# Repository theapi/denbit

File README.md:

# Denbit
Training wheels for the NodeMCU
-------------------------------------------------------------

##Installation

- Download and install the [Aduino IDE](https://www.arduino.cc/en/Main/Software) plus any drivers it asks too. 
 You can use the free version with the `JUST DOWNLOAD` link. No need to donate money.

- Install the NodeMCU "board" into the Arduino IDE:
 - Start Arduino and open Preferences window.
 - Enter http://arduino.esp8266.com/stable/package_esp8266com_index.json into Additional Board Manager URLs field and click `Ok`:

 - Open the Boards Manager `Tools > Board > Boards Manager...`:

 - Scroll down to `esp8266 by ESP8266 Community`, click `More info` and select version 2.2.0 then click install:

 - Click `Close` once it installed

 - Select the NodeMCU 1.0 board from `Tools > Board menu` and select `NodeMCU 1.0 (ESP-12E Module)`:

- Install the denbit library 
 - [Download the latest release of this repo](https://github.com/theapi/denbit/archive/v1.0.9.zip)
 - `Sketch -> Include Library -> Add .ZIP Library...` then select the file downloaded in the step above.
 
- Rename ~/Documents/Arduino/libraries/denbit/src/default_config.h to config.h
and edit its content to have the wifi access details and your denbit's name.

- Mac users, if programming with a usb cable, install the driver from [www.silabs.com][1] ([direct link][2]).

## Make it do something...
- Connect the denbit to the usb port of the computer.
- Select the `Port` the usb is connected to
 - On a Mac it will be `/dev/cu.SLAB_USBtoUART` 
 - On Windows it will be `COMM` and a number so something like `COMM4`
- Load the Blink "sketch"
 - `File -> Examples -> Denbit -> Basics -> Blink`
 - Compile (verify) the software: click the tick in the top left of the Arduino application... 

 - wait while it compiles...

 - Upload the software: click the arrow in the top left of the Arduino application:

 - wait while it uploads...

  - The center light will be blue while it uploads. 

  - When the Arduino window says *"Done uploading"* the green light will blink on & off
 - Change the Blink sketch so that `delay(1000)` is `delay(500)`, then compile & upload again. The green LED will now blink twice as fast

## Play with the Denbit Basic examples
- [Fade](docs/examples/Basics/Fade.md)
- [DigitalReadSerial](docs/examples/Basics/DigitalReadSerial.md)
- [AnalogReadSerial](docs/examples/Basics/AnalogReadSerial.md)
- [Denbit](docs/examples/Basics/Denbit.md)
- [Knob](docs/examples/Basics/Knob.md)

## Play with servos
- [ServoSweep](docs/examples/Servo/ServoSweep.md)
- [ServoKnob](docs/examples/Servo/ServoKnob.md)

## Then use some sensors
- [Temperature](docs/examples/Sensors/Temperature.md)
- [Knock](docs/examples/Sensors/Knock.md)

[1]:https://www.silabs.com/products/mcu/Pages/USBtoUARTBridgeVCPDrivers.aspx
[2]:https://www.silabs.com/Support%20Documents/Software/Mac_OSX_VCP_Driver.zip

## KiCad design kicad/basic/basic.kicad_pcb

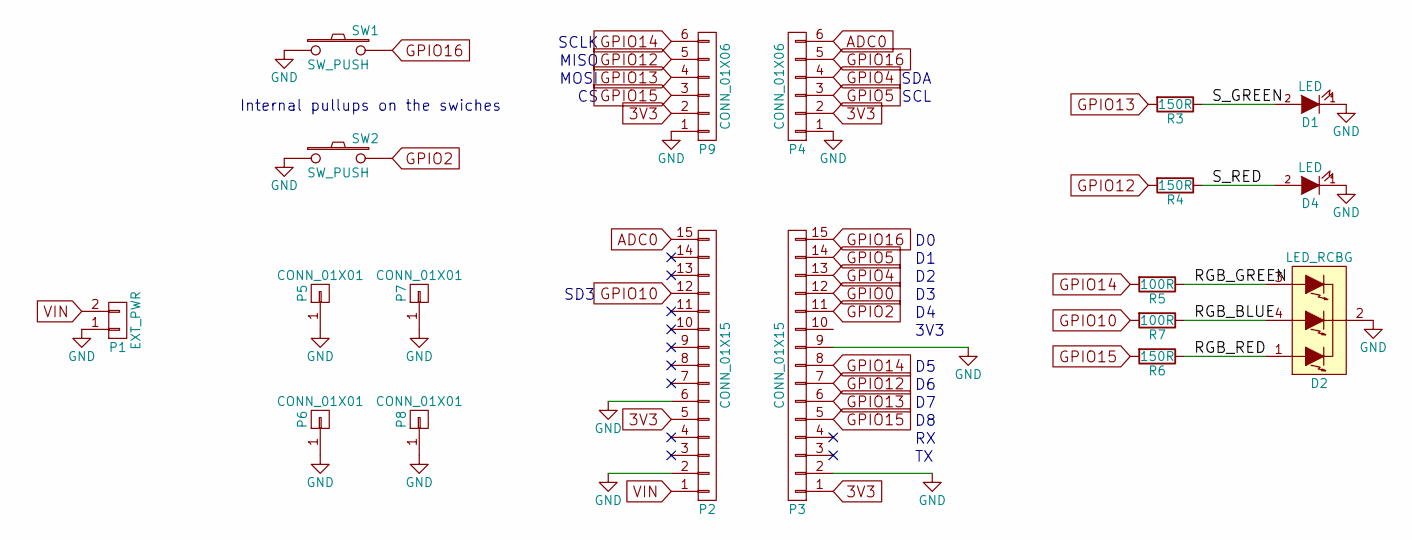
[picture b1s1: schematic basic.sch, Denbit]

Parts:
D1, D4: LED; LED-5MM
D2: LED_RCBG; LED-RGB-5MM_Common_Cathode
P1: EXT_PWR; Pin_Header_Straight_1x02
P2, P3: CONN_01X15; Socket_Strip_Straight_1x15
P4, P9: CONN_01X06; Socket_Strip_Straight_1x06
P5, P6, P7, P8: CONN_01X01; MountingHole_3.2mm_M3_ISO14580_Pad
R3, R4, R6: 150R; Resistor_Horizontal_RM10mm
R5, R7: 100R; Resistor_Horizontal_RM10mm
SW1, SW2: SW_PUSH; SW_PUSH_SMALL

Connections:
3V3: P2.5, P3.1, P4.2, P9.2
/RGB_BLUE: D2.4 (GREEN_ANODE), R7.1
/RGB_GREEN: D2.3 (BLUE_ANODE), R5.1
/RGB_RED: D2.1 (RED_ANODE), R6.1
/S_GREEN: D1.2 (A), R3.1
/S_RED: D4.2 (A), R4.1
ADC0: P2.15, P4.6
GND: D1.1 (K), D2.2 (COMMON_CATHODE), D4.1 (K), P1.1, P2.2, P2.6, P3.2, P3.9, P4.1, P5.1, P6.1, P7.1, P8.1, P9.1, SW1.1, SW2.1
GPIO0: P3.12
GPIO2: P3.11, SW2.2
GPIO4: P3.13, P4.4
GPIO5: P3.14, P4.3
GPIO10: P2.12, R7.2
GPIO12: P3.7, P9.5, R4.2
GPIO13: P3.6, P9.4, R3.2
GPIO14: P3.8, P9.6, R5.2
GPIO15: P3.5, P9.3, R6.2
GPIO16: P3.15, P4.5, SW1.2
VIN: P1.2, P2.1

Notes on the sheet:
MISO
SCLK
MOSI
SDA
SCL
3V3
SD3
Internal pullups on the swiches

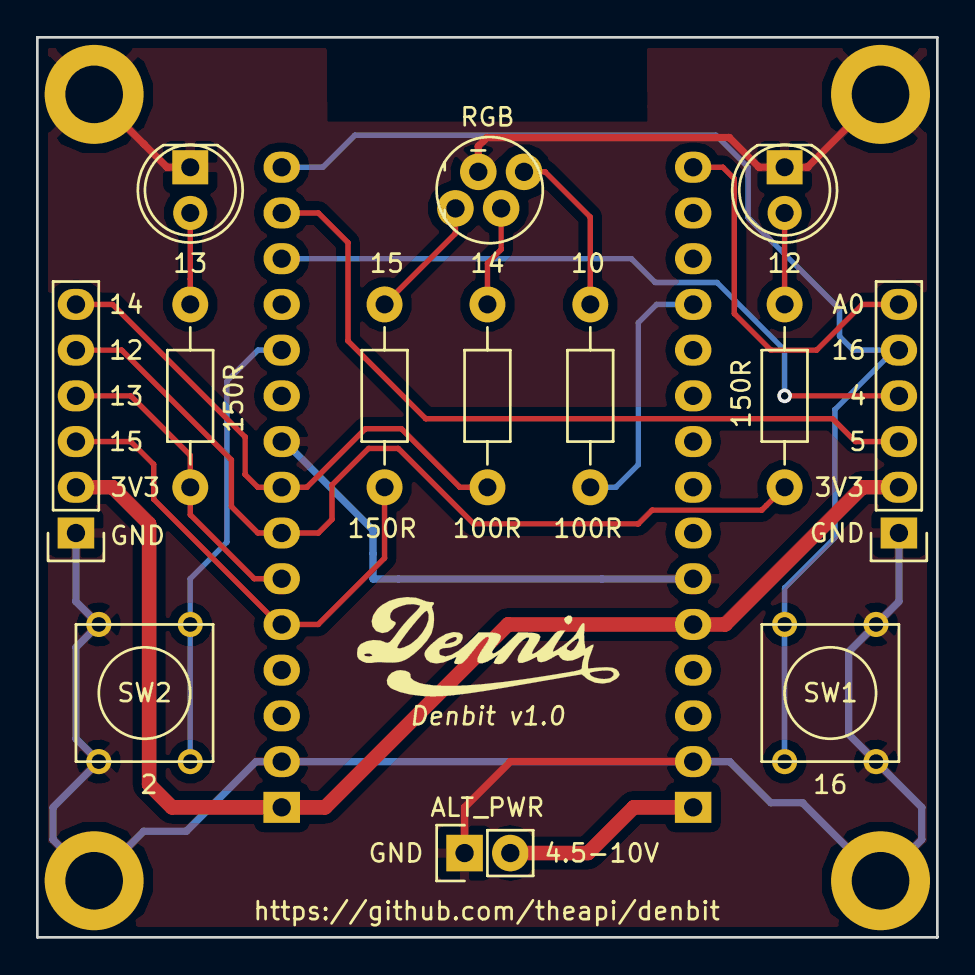
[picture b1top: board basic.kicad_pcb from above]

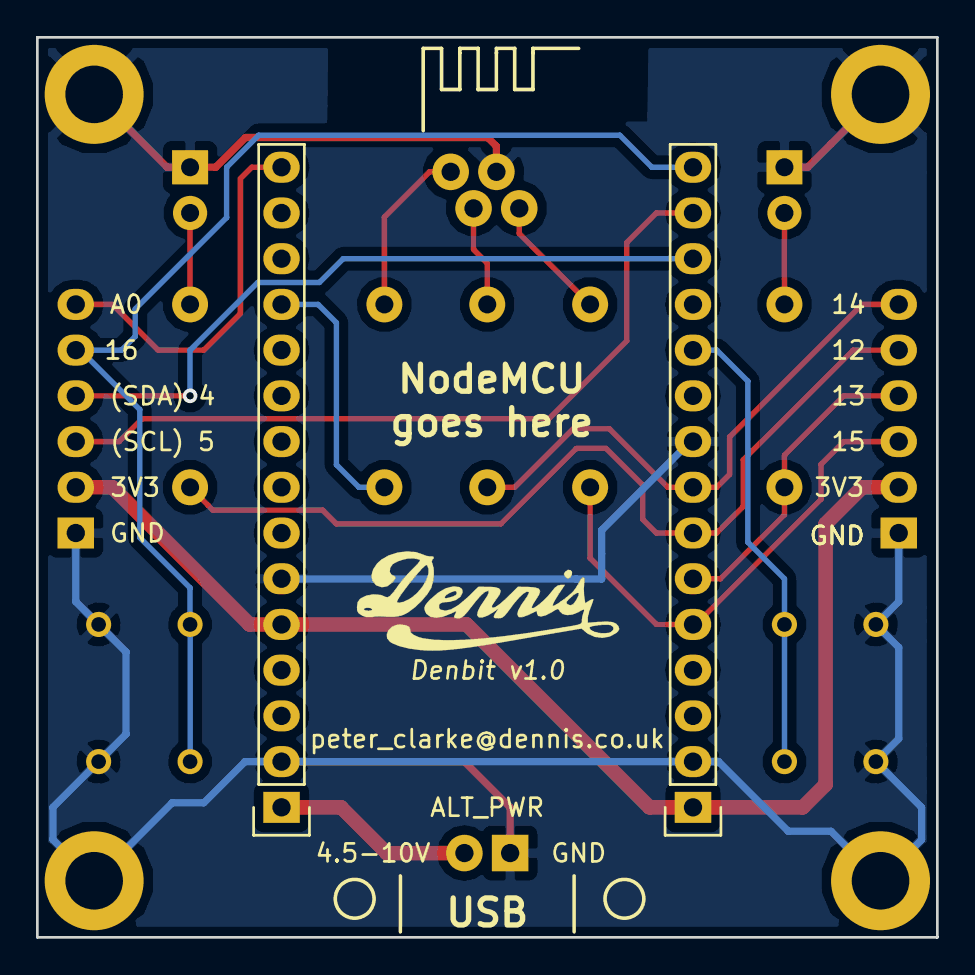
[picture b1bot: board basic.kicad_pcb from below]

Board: 2 copper layers, 50.0 x 50.0 mm, 19 parts (2 on the bottom side), 18 nets.

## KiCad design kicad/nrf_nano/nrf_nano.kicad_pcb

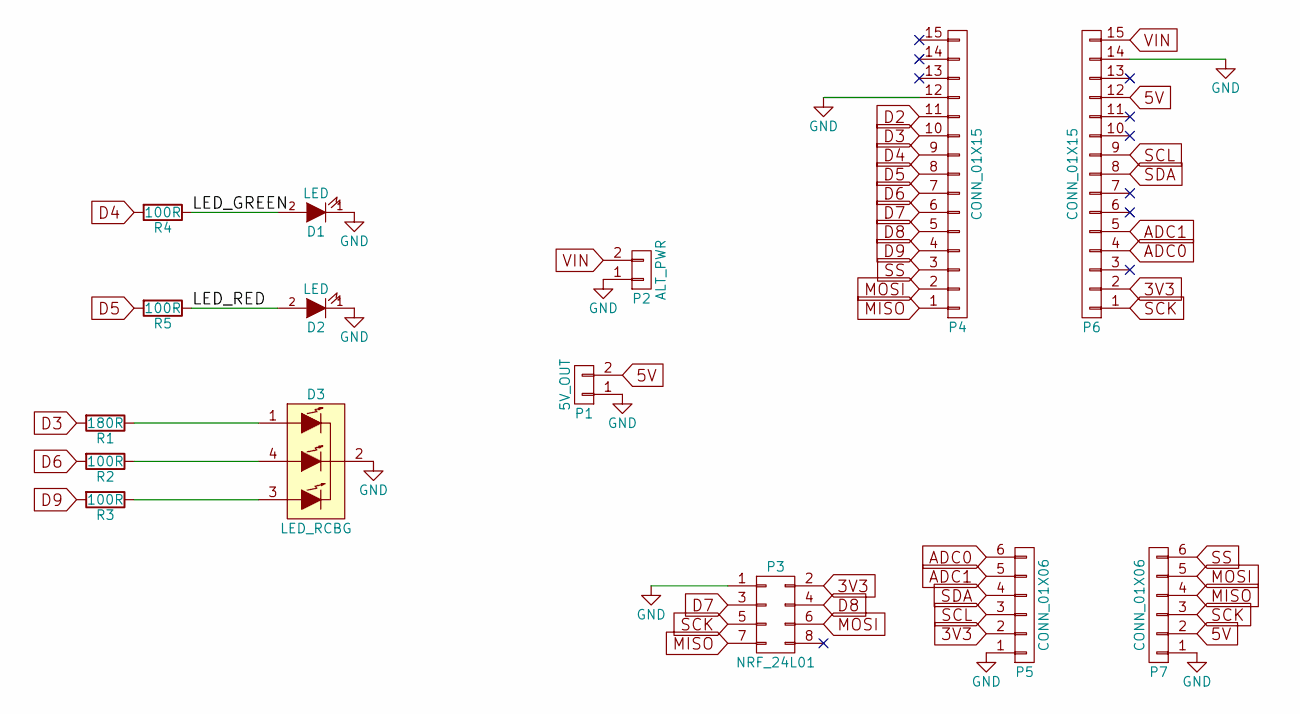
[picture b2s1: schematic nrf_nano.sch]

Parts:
D1, D2: LED; LED-5MM
D3: LED_RCBG; LED-RGB-5MM_Common_Cathode
P1: 5V_OUT; Socket_Strip_Straight_1x02
P2: ALT_PWR; Pin_Header_Straight_1x02
P3: NRF_24L01; Socket_Strip_Straight_2x04
P4, P6: CONN_01X15; Socket_Strip_Straight_1x15
P5, P7: CONN_01X06; Socket_Strip_Straight_1x06
R1: 180R; Resistor_Horizontal_RM10mm
R2, R3, R4, R5: 100R; Resistor_Horizontal_RM10mm

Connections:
3V3: P3.2, P5.2, P6.2
5V: P1.2, P6.12, P7.2
/LED_GREEN: D1.2 (A), R4.1
/LED_RED: D2.2 (A), R5.1
ADC0: P5.6, P6.4
ADC1: P5.5, P6.5
D2: P4.11
D3: P4.10, R1.2
D4: P4.9, R4.2
D5: P4.8, R5.2
D6: P4.7, R2.2
D7: P3.3, P4.6
D8: P3.4, P4.5
D9: P4.4, R3.2
GND: D1.1 (K), D2.1 (K), D3.2 (COMMON_CATHODE), P1.1, P2.1, P3.1, P4.12, P5.1, P6.14, P7.1
MISO: P3.7, P4.1, P7.4
MOSI: P3.6, P4.2, P7.5
unnamed: D3.1 (RED_ANODE), R1.1
unnamed: D3.3 (BLUE_ANODE), R3.1
unnamed: D3.4 (GREEN_ANODE), R2.1
SCK: P3.5, P6.1, P7.3
SCL: P5.3, P6.9
SDA: P5.4, P6.8
SS: P4.3, P7.6
VIN: P2.2, P6.15

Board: 2 copper layers, 15 parts (2 on the bottom side), 24 nets, no tracks yet.

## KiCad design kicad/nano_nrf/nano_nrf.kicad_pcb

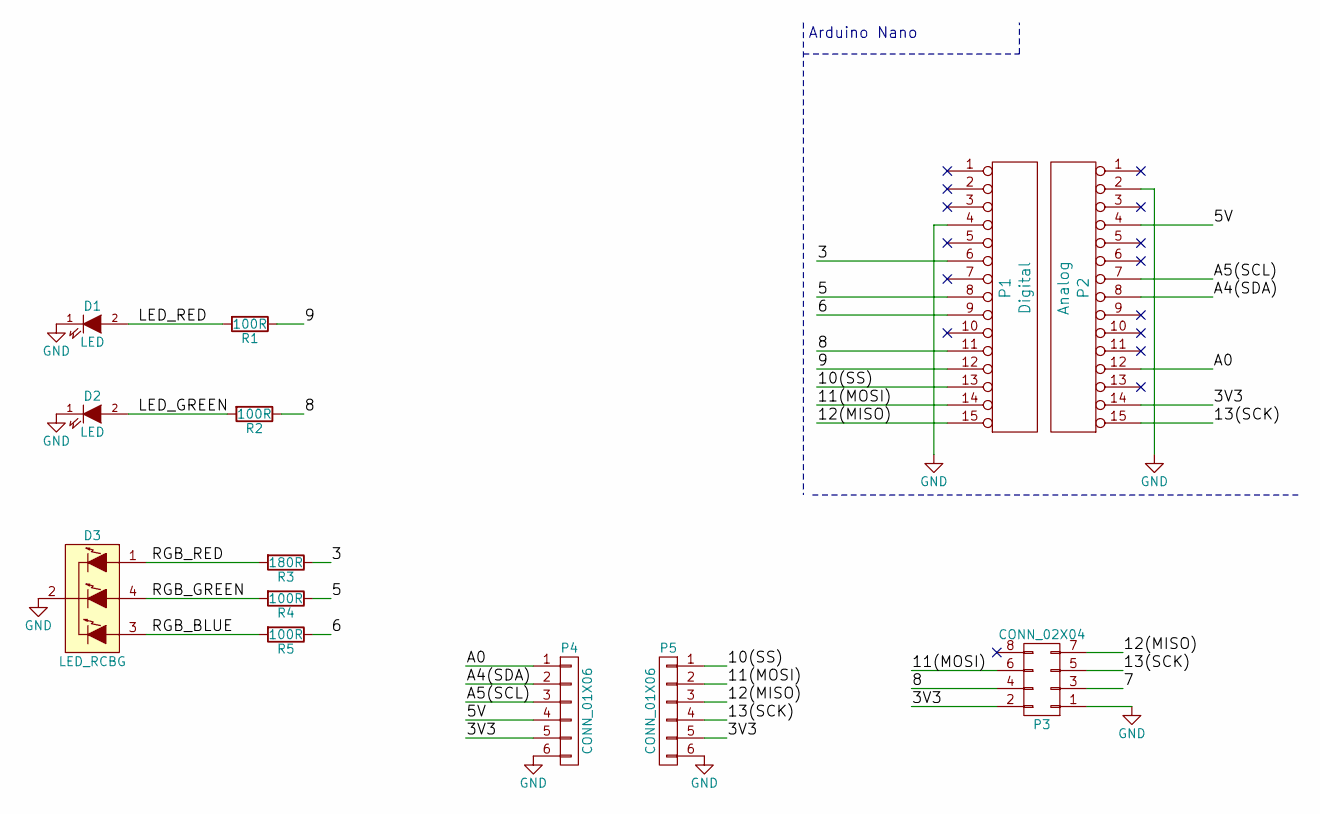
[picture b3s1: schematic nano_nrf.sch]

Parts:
D1, D2: LED; LED-5MM
D3: LED_RCBG; LED-RGB-5MM_Common_Cathode
P1: Digital; Socket_Strip_Straight_1x15
P2: Analog; Socket_Strip_Straight_1x15
P3: CONN_02X04; Socket_Strip_Straight_2x04
P4, P5: CONN_01X06; Socket_Strip_Straight_1x06
R1, R2, R4, R5: 100R; Resistor_Horizontal_RM10mm
R3: 180R; Resistor_Horizontal_RM10mm

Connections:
/3: P1.6, R3.1
/3V3: P2.14, P3.2, P4.5, P5.5
/5: P1.8, R4.1
/5V: P2.4, P4.4
/6: P1.9, R5.1
/7: P3.3
/8: P1.11, P3.4, R2.1
/9: P1.12, R1.1
/10(SS): P1.13, P5.1
/11(MOSI): P1.14, P3.6, P5.2
/12(MISO): P1.15 (p15), P3.7, P5.3
/13(SCK): P2.15 (p15), P3.5, P5.4
/A0: P2.12, P4.1
/A4(SDA): P2.8, P4.2
/A5(SCL): P2.7, P4.3
/LED_GREEN: D2.2 (A), R2.2
/LED_RED: D1.2 (A), R1.2
/RGB_BLUE: D3.3 (BLUE_ANODE), R5.2
/RGB_GREEN: D3.4 (GREEN_ANODE), R4.2
/RGB_RED: D3.1 (RED_ANODE), R3.2
GND: D1.1 (K), D2.1 (K), D3.2 (COMMON_CATHODE), P1.4, P2.2, P3.1, P4.6, P5.6

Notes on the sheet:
Arduino Nano

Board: 2 copper layers, 14 parts (2 on the bottom side), 20 nets, no tracks yet.

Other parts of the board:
P6: CONN_1; 1pin_Nano

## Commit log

2016-04-14 Initial thoughts
2016-04-14 Breakout only the GPIO
2016-04-14 Through hole parts
2016-04-14 Wider nodemcu footprint
2016-04-14 Labeling
2016-04-14 Swapped headers
2016-04-14 Corrected footprint width
2016-04-14 Routing
2016-04-15 Dennis logo
2016-04-15 Orientation markers
2016-04-15 Gerbers
2016-04-15 RGB led
2016-04-16 Layout tweaks
2016-04-16 ESP8266 datasheet
2016-04-16 Resistor values
2016-04-16 SmokeTest
2016-04-16 Changed pin assignments
2016-04-16 Use arduino pin numbers & breakout I2C & SPI
2016-04-17 I2C & SPI on the headers
2016-04-17 Pin tweaks
2016-04-17 Internal pullup on the switches
2016-04-18 Renders
2016-04-18 Switch silkscreen labels
2016-04-18 Connect the right switch to the header
2016-04-18 Serial print values
2016-04-18 NodeMCU schematic
2016-04-19 Use gpio16 instead of gpio0
2016-04-19 Start of nano with nrf24l01
2016-04-19 Leds
2016-04-19 Nano on the bottom
2016-04-19 Switch on GPIO16
2016-04-19 Swap SDA & SCL on the header
2016-04-19 Tweaked labels
2016-04-19 Swap SDA & SCL
2016-04-20 External power
2016-04-20 Nrf24L01 with arduino nano
2016-04-20 Switches
2016-04-21 Wireless access point demo
2016-04-24 Led position tweak & silkscreen adjustments
2016-04-25 File extension change
2016-04-25 Staggered RGB led leads
2016-04-25 Offset the led pads
2016-04-25 Same size holes as regular leds
2016-04-26 Mils not mm
2016-04-26 gerber zip
2016-04-26 PCB screen shot
2016-04-27 Re-exported gerbers due to makerstudio.cc request
2016-04-27 Without extended headers
2016-04-28 Start of Arduino library
2016-04-28 Empty library source files
2016-05-02 Knock sensor
2016-05-02 Initialise the Denbit with the library
2016-05-02 Namespaced defines
2016-05-02 Servo Sweep
2016-05-03 Comment tweak
2016-05-03 Start of websocket controlled servo
2016-05-07 OLED screen 128x64 I2C demo
2016-05-07 Use the denbit library too
2016-05-07 Show the Dennis logo
2016-05-07 Where to get the library
2016-05-07 Soil Sensor
2016-05-10 Installation instructions
2016-05-11 Basic setup
2016-05-12 Seperate file fo the html
2016-05-14 Better library link
2016-05-23 Use the library
2016-05-23 Access point rather than connect to existing network
2016-05-23 Control the servo with the phone accelerometer
2016-05-25 Start of ball interface
2016-06-01 Experimenting with velocity
2016-06-01 Alpha too
2016-06-13 No pullup on pin 16
2016-06-13 Basic examples
2016-06-13 Move to examples
2016-06-13 Ignore silly mac stuff
2016-06-13 Denbit demo
2016-06-13 Fritzing
2016-06-13 Denbit part for Fritzing
2016-06-13 Knock
2016-06-14 Temperature & Light sensors
2016-06-14 Start of example docs
2016-06-14 Knob example
2016-06-14 Analog read fritzing
2016-06-14 Moved images
2016-06-14 Move docs
2016-06-15 Smaller denbit image
2016-06-15 Board manager url input image
2016-06-15 Board manager select image
2016-06-15 Board manager image
2016-06-15 Board selected image
2016-06-15 Smaller resolution
2016-06-15 Image clean up
2016-06-15 Link to doc
2016-06-15 Images & links
2016-06-15 Compiling image
2016-06-15 Images
2016-06-15 Resolution
2016-06-16 Temperature
2016-06-16 Organising
2016-06-16 Readme
2016-06-21 Temperature server
2016-06-21 Show degrees C
2016-07-21 Simple GET request
2016-07-25 MQTT
2016-07-25 Temperature over MQTT
2016-07-26 Temperature over MQTT and Websockets
2016-08-20 Sonar (ping) sensor HC-SR04
2016-08-20 Servo controlled by a potentiometer
2016-08-20 Servo images
2016-09-09 Ensure that previous wifi settings are removed
2016-10-13 OTA config
2016-10-13 OTAhandle
2016-10-14 Use the default name if the config did not get changed
2016-10-14 Basics with OTA
2016-10-21 Separate examples for OTA
2016-10-27 Update OLED demo
